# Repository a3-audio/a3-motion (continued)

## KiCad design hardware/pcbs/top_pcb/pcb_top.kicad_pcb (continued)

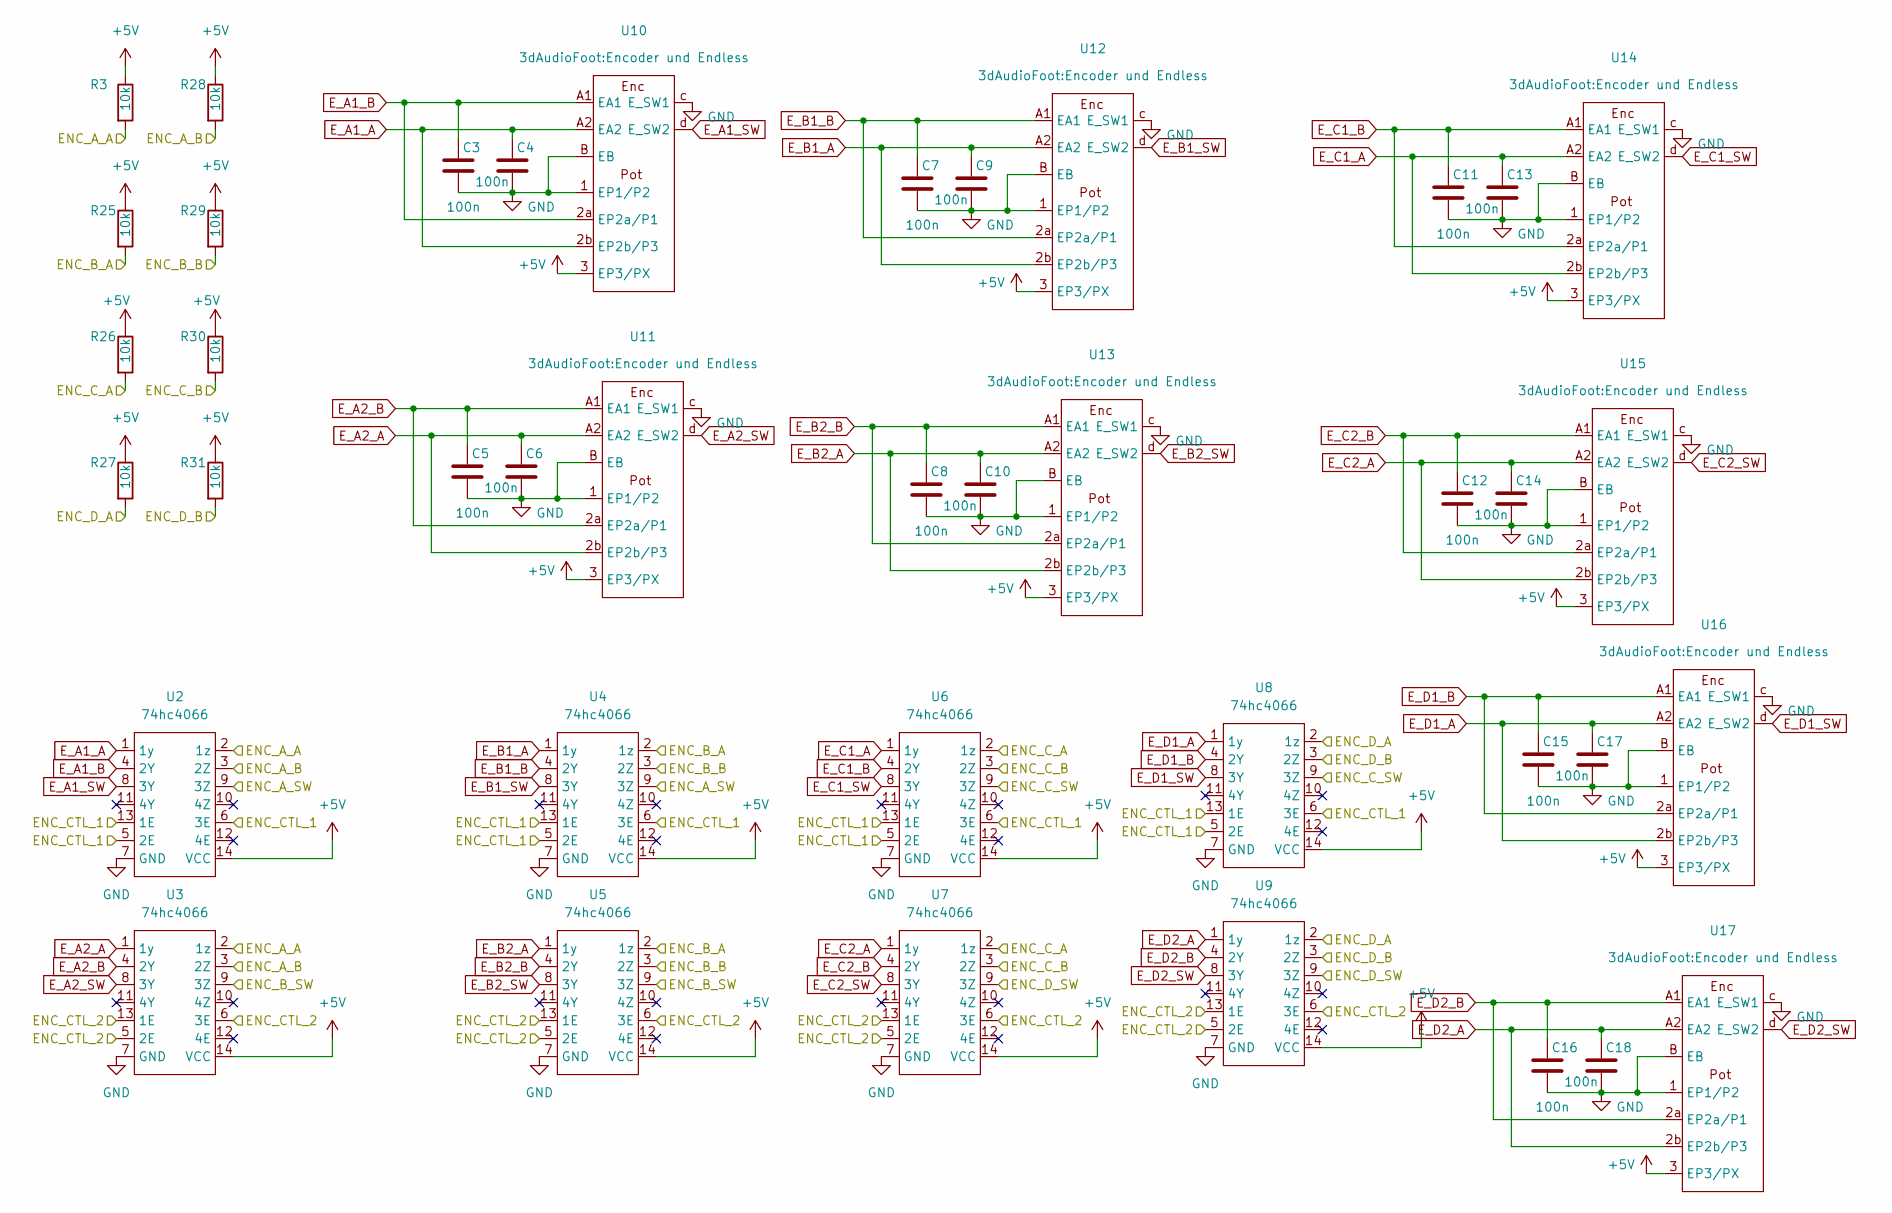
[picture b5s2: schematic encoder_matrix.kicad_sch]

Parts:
C3, C4, C5, C6, C7, C8, C9, C10, C11, C12, C13, C14, C15, C16, C17, C18: 100n; C_1206_3216Metric_Pad1.33x1.80mm_HandSolder
R3, R25, R26, R27, R28, R29, R30, R31: 10k; R_1206_3216Metric_Pad1.30x1.75mm_HandSolder
U2, U3, U4, U5, U6, U7, U8, U9: 74hc4066; SOIC-14_3.9x8.7mm_P1.27mm
U10, U11, U12, U13, U14, U15, U16, U17: Encoder und Endless

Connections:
/Untitled Sheet/ENC_A_A: R3.2, U2.2 (1z), U3.2 (1z); also elsewhere on the board
/Untitled Sheet/ENC_A_B: R28.2, U2.3 (2Z), U3.3 (2Z); also elsewhere on the board
/Untitled Sheet/ENC_A_SW: U2.9 (3Z), U4.9 (3Z); also elsewhere on the board
/Untitled Sheet/ENC_B_A: R25.2, U4.2 (1z), U5.2 (1z); also elsewhere on the board
/Untitled Sheet/ENC_B_B: R29.2, U4.3 (2Z), U5.3 (2Z); also elsewhere on the board
/Untitled Sheet/ENC_B_SW: U3.9 (3Z), U5.9 (3Z); also elsewhere on the board
/Untitled Sheet/ENC_CTL_1: U2.5 (2E), U2.6 (3E), U2.13 (1E), U4.5 (2E), U4.6 (3E), U4.13 (1E), U6.5 (2E), U6.6 (3E), U6.13 (1E), U8.5 (2E), U8.6 (3E), U8.13 (1E); also elsewhere on the board
/Untitled Sheet/ENC_CTL_2: U3.5 (2E), U3.6 (3E), U3.13 (1E), U5.5 (2E), U5.6 (3E), U5.13 (1E), U7.5 (2E), U7.6 (3E), U7.13 (1E), U9.5 (2E), U9.6 (3E), U9.13 (1E); also elsewhere on the board
/Untitled Sheet/ENC_C_A: R26.2, U6.2 (1z), U7.2 (1z); also elsewhere on the board
/Untitled Sheet/ENC_C_B: R30.2, U6.3 (2Z), U7.3 (2Z); also elsewhere on the board
/Untitled Sheet/ENC_C_SW: U6.9 (3Z), U8.9 (3Z); also elsewhere on the board
/Untitled Sheet/ENC_D_A: R27.2, U8.2 (1z), U9.2 (1z); also elsewhere on the board
/Untitled Sheet/ENC_D_B: R31.2, U8.3 (2Z), U9.3 (2Z); also elsewhere on the board
/Untitled Sheet/ENC_D_SW: U7.9 (3Z), U9.9 (3Z); also elsewhere on the board
E_A1_A: C4.1, U2.1 (1y), U10.2b (EP2b/P3), U10.A2 (EA2)
E_A1_B: C3.1, U2.4 (2Y), U10.2a (EP2a/P1), U10.A1 (EA1)
E_A1_SW: U2.8 (3Y), U10.d (E_SW2)
E_A2_A: C6.1, U3.1 (1y), U11.2b (EP2b/P3), U11.A2 (EA2)
E_A2_B: C5.1, U3.4 (2Y), U11.2a (EP2a/P1), U11.A1 (EA1)
E_A2_SW: U3.8 (3Y), U11.d (E_SW2)
E_B1_A: C9.1, U4.1 (1y), U12.2b (EP2b/P3), U12.A2 (EA2)
E_B1_B: C7.1, U4.4 (2Y), U12.2a (EP2a/P1), U12.A1 (EA1)
E_B1_SW: U4.8 (3Y), U12.d (E_SW2)
E_B2_A: C10.1, U5.1 (1y), U13.2b (EP2b/P3), U13.A2 (EA2)
E_B2_B: C8.1, U5.4 (2Y), U13.2a (EP2a/P1), U13.A1 (EA1)
E_B2_SW: U5.8 (3Y), U13.d (E_SW2)
E_C1_A: C13.1, U6.1 (1y), U14.2b (EP2b/P3), U14.A2 (EA2)
E_C1_B: C11.1, U6.4 (2Y), U14.2a (EP2a/P1), U14.A1 (EA1)
E_C1_SW: U6.8 (3Y), U14.d (E_SW2)
E_C2_A: C14.1, U7.1 (1y), U15.2b (EP2b/P3), U15.A2 (EA2)
E_C2_B: C12.1, U7.4 (2Y), U15.2a (EP2a/P1), U15.A1 (EA1)
E_C2_SW: U7.8 (3Y), U15.d (E_SW2)
E_D1_A: C17.1, U8.1 (1y), U16.2b (EP2b/P3), U16.A2 (EA2)
E_D1_B: C15.1, U8.4 (2Y), U16.2a (EP2a/P1), U16.A1 (EA1)
E_D1_SW: U8.8 (3Y), U16.d (E_SW2)
E_D2_A: C18.1, U9.1 (1y), U17.2b (EP2b/P3), U17.A2 (EA2)
E_D2_B: C16.1, U9.4 (2Y), U17.2a (EP2a/P1), U17.A1 (EA1)
E_D2_SW: U9.8 (3Y), U17.d (E_SW2)
GND: C3.2, C4.2, C5.2, C6.2, C7.2, C8.2, C9.2, C10.2, C11.2, C12.2, C13.2, C14.2, C15.2, C16.2, C17.2, C18.2, U2.7 (GND), U3.7 (GND), U4.7 (GND), U5.7 (GND), U6.7 (GND), U7.7 (GND), U8.7 (GND), U9.7 (GND), U10.1 (EP1/P2), U10.B (EB), U10.c (E_SW1), U11.1 (EP1/P2), U11.B (EB), U11.c (E_SW1), U12.1 (EP1/P2), U12.B (EB), U12.c (E_SW1), U13.1 (EP1/P2), U13.B (EB), U13.c (E_SW1), U14.1 (EP1/P2), U14.B (EB), U14.c (E_SW1), U15.1 (EP1/P2), U15.B (EB), U15.c (E_SW1), U16.1 (EP1/P2), U16.B (EB), U16.c (E_SW1), U17.1 (EP1/P2), U17.B (EB), U17.c (E_SW1); also elsewhere on the board
VCC: R3.1, R25.1, R26.1, R27.1, R28.1, R29.1, R30.1, R31.1, U2.14 (VCC), U3.14 (VCC), U4.14 (VCC), U5.14 (VCC), U6.14 (VCC), U7.14 (VCC), U8.14 (VCC), U9.14 (VCC), U10.3 (EP3/PX), U11.3 (EP3/PX), U12.3 (EP3/PX), U13.3 (EP3/PX), U14.3 (EP3/PX), U15.3 (EP3/PX), U16.3 (EP3/PX), U17.3 (EP3/PX); also elsewhere on the board

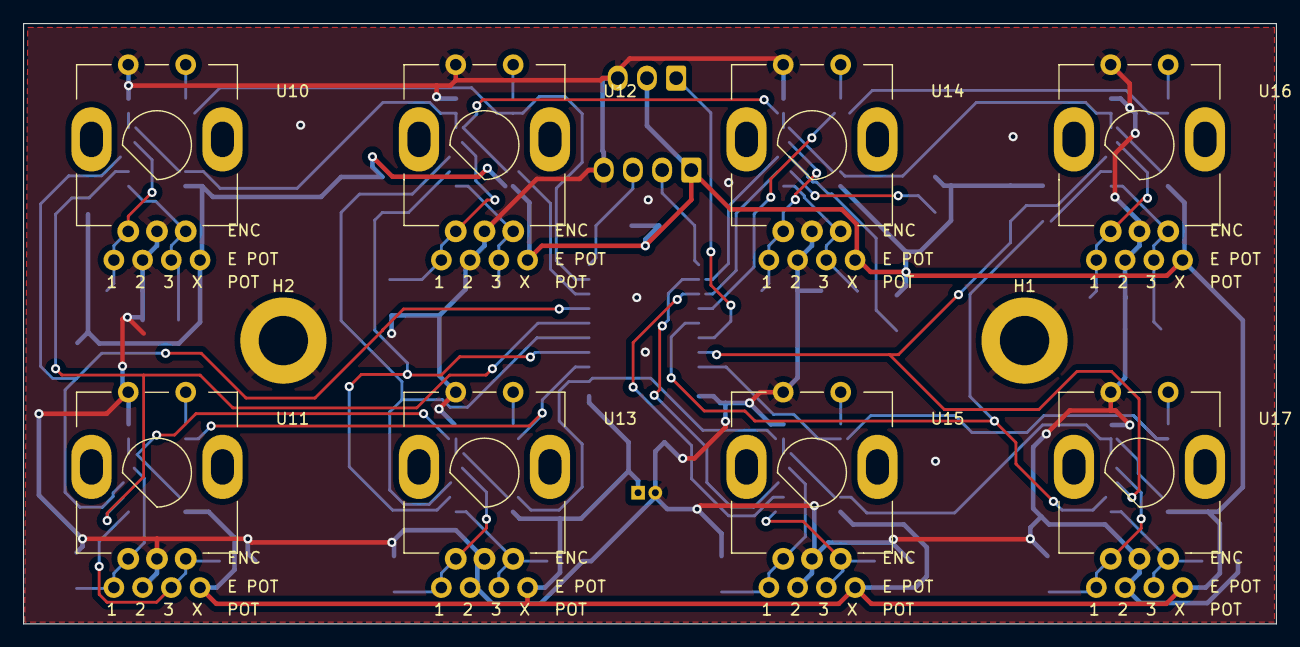
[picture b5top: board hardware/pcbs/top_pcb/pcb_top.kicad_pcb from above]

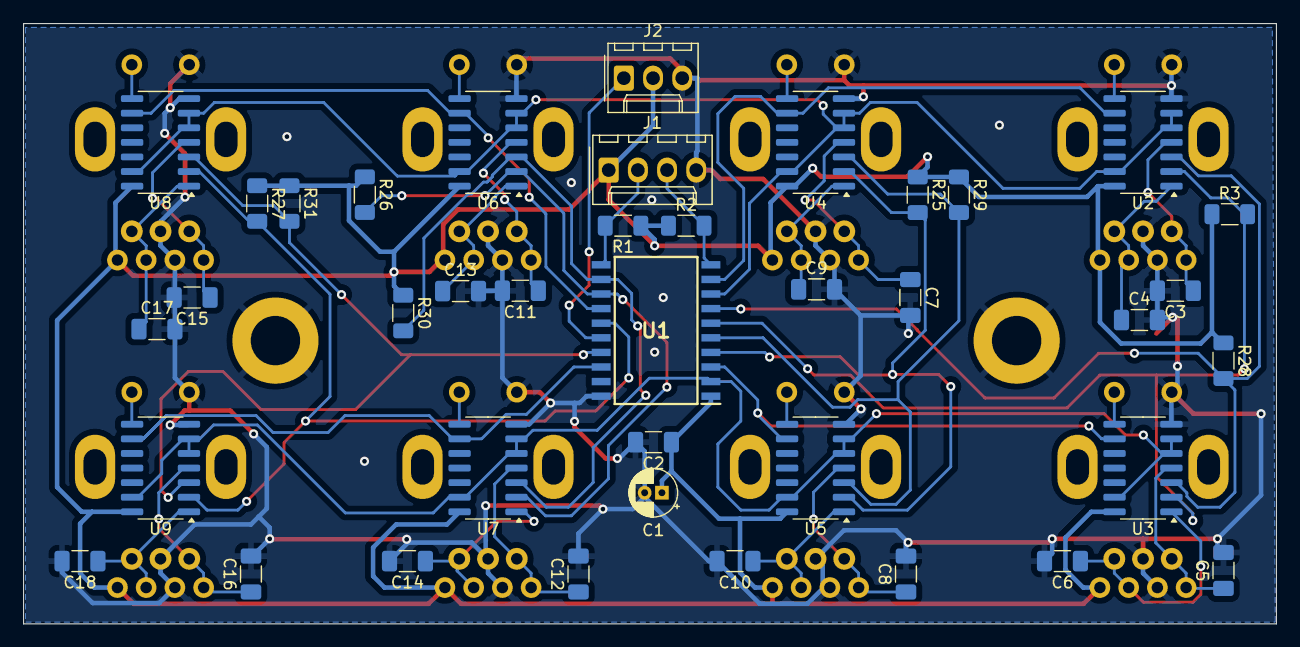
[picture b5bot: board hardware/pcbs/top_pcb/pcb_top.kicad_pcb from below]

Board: 2 copper layers, 109.0 x 52.2 mm, 49 parts (39 on the bottom side), 43 nets.

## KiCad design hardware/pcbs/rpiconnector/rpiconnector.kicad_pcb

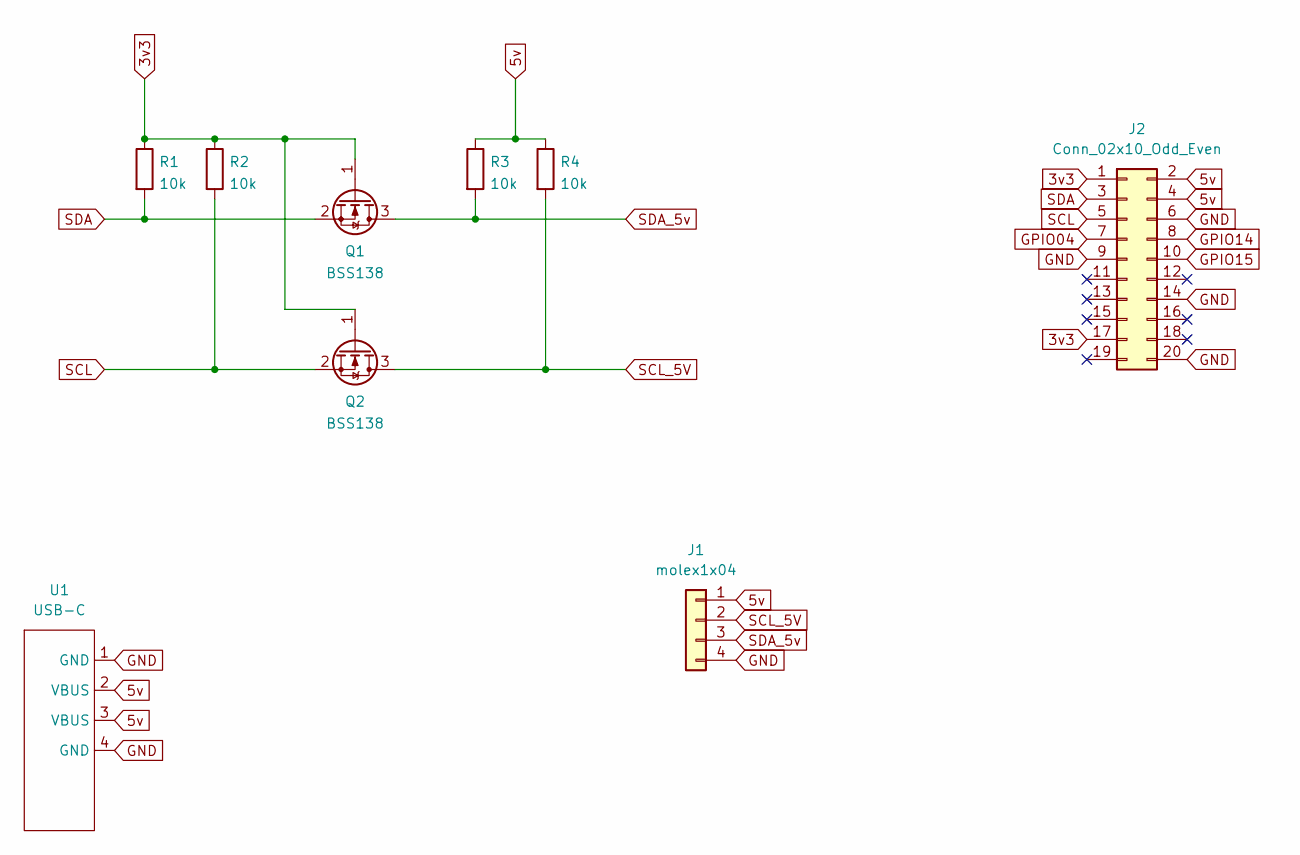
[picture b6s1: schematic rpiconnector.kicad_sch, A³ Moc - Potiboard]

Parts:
J1: molex1x04; Molex_KK-254_AE-6410-04A_1x04_P2.54mm_Vertical
J2: Conn_02x10_Odd_Even; PinSocket_2x10_P2.54mm_Vertical
Q1, Q2: BSS138
R1, R2, R3, R4: 10k; R_1206_3216Metric_Pad1.30x1.75mm_HandSolder
U1: USB-C; USB-C simple

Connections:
3v3: J2.1, J2.17, Q1.1 (G), Q2.1 (G), R1.1, R2.1
5v: J1.1, J2.2, J2.4, R3.1, R4.1, U1.2 (VBUS), U1.3 (VBUS)
GND: J1.4, J2.6, J2.9, J2.14, J2.20, U1.1 (GND), U1.4 (GND)
GPIO04: J2.7
GPIO14: J2.8
GPIO15: J2.10
SCL: J2.5, Q2.2 (S), R2.2
SCL_5V: J1.2, Q2.3 (D), R4.2
SDA: J2.3, Q1.2 (S), R1.2
SDA_5v: J1.3, Q1.3 (D), R3.2

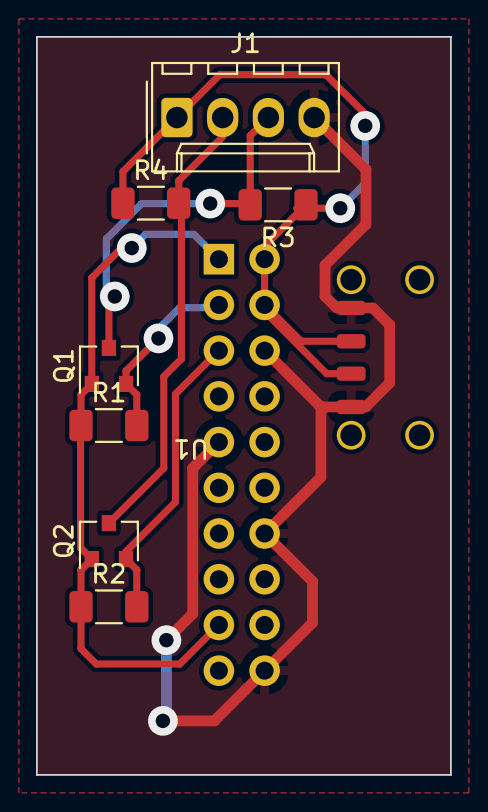
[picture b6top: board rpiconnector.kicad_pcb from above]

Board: 2 copper layers, 23.0 x 41.0 mm, 9 parts (1 on the bottom side), 7 nets.

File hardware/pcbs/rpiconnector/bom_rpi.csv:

"Reference","Value","Datasheet","Footprint","Qty","DNP"
"J1","molex1x04","~","Connector_Molex:Molex_KK-254_AE-6410-04A_1x04_P2.54mm_Vertical","1",""
"J2","Conn_02x10_Odd_Even","~","Connector_PinSocket_2.54mm:PinSocket_2x10_P2.54mm_Vertical","1",""
"Q1,Q2","BSS138","https://www.onsemi.com/pub/Collateral/BSS138-D.PDF","3dAudioFoot:BSS138","2",""
"R1,R2,R3,R4","10k","~","Resistor_SMD:R_1206_3216Metric_Pad1.30x1.75mm_HandSolder","4",""
"U1","USB-C","","3dAudioFoot:USB-C","1",""

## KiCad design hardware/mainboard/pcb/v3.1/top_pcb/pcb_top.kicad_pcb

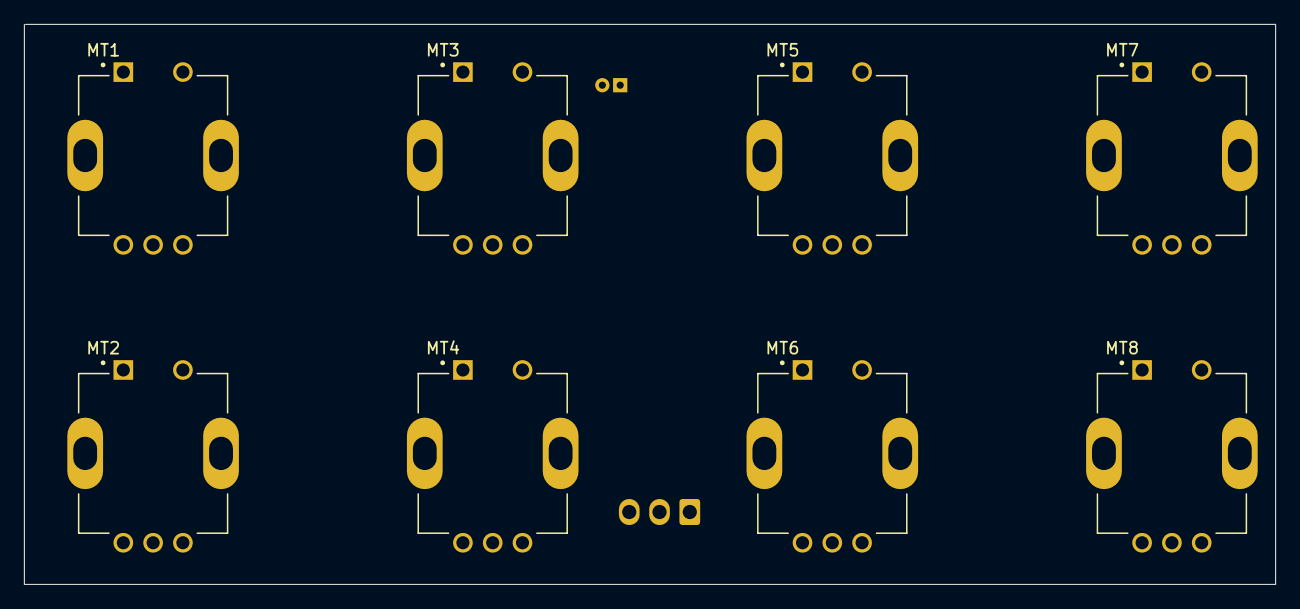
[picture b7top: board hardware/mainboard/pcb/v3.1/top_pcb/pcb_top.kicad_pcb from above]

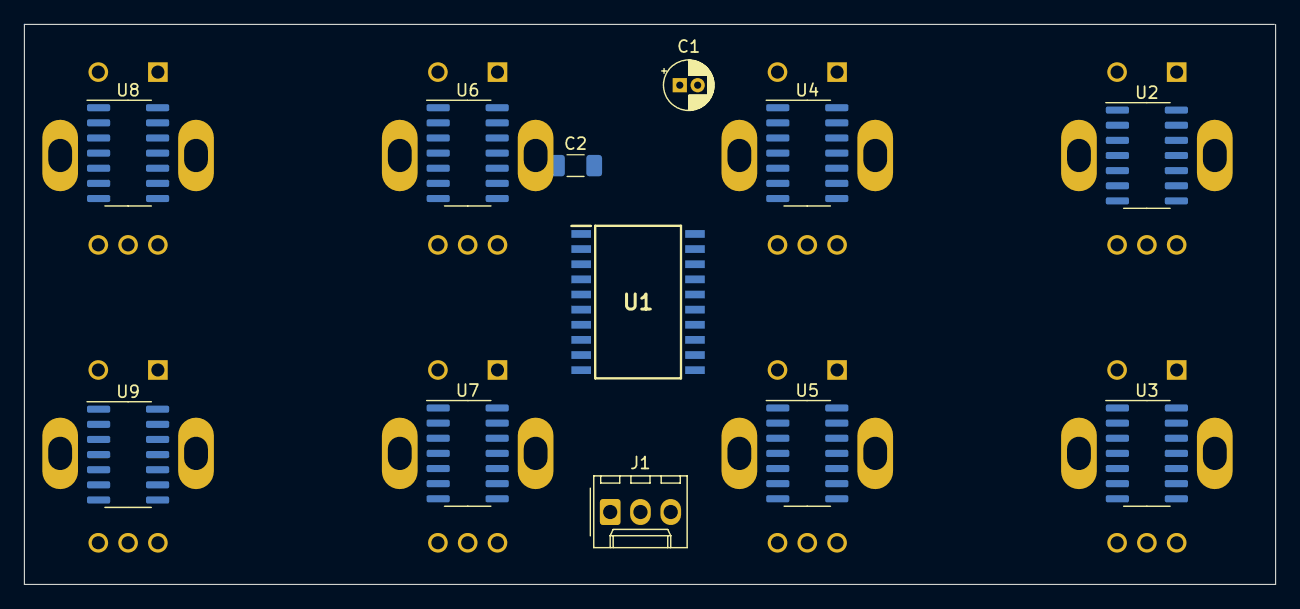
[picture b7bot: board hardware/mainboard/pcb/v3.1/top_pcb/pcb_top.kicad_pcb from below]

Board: 2 copper layers, 105.0 x 47.0 mm, 20 parts (12 on the bottom side), 43 nets, no tracks yet.

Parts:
C1: 10uF; CP_Radial_D4.0mm_P1.50mm
C2: 100nF; C_1206_3216Metric_Pad1.33x1.80mm_HandSolder
J1: molex1x03; Molex_KK-254_AE-6410-03A_1x03_P2.54mm_Vertical
MT1, MT2, MT3, MT4, MT5, MT6, MT7, MT8: PEC11R-4215F-S0024; XDCR_PEC11R-4215F-S0024
U1: ATtiny1626; attiny1626
U2, U3, U4, U5, U6, U7, U8, U9: 74hc4066; SOIC-14_3.9x8.7mm_P1.27mm

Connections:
+5V: C1.1, C2.1, U1.1 (VCC), U2.14 (VCC), U3.14 (VCC), U4.14 (VCC), U5.14 (VCC), U6.14 (VCC), U7.14 (VCC), U8.14 (VCC), U9.14 (VCC)
/Untitled Sheet/ENC_A_A: U1.4 (PA6/ADC6), U2.2 (1z), U3.2 (1z)
/Untitled Sheet/ENC_A_B: U1.5 (PA7/ADC7), U2.3 (2Z), U3.3 (2Z)
/Untitled Sheet/ENC_A_SW: U1.6 (PB5/ADC8/CLKOUT), U2.9 (3Z), U3.9 (3Z)
/Untitled Sheet/ENC_B_A: U1.7 (PB4/ADC9/RST), U4.2 (1z), U5.2 (1z)
/Untitled Sheet/ENC_B_B: U1.8 (PB3), U4.3 (2Z), U5.3 (2Z)
/Untitled Sheet/ENC_B_SW: U1.9 (PB2), U4.9 (3Z), U5.9 (3Z)
/Untitled Sheet/ENC_CTL_1: U1.2 (PA4/ADC4/SS1), U2.5 (2E), U2.6 (3E), U2.13 (1E), U4.5 (2E), U4.6 (3E), U4.13 (1E), U6.5 (2E), U6.6 (3E), U6.13 (1E), U8.5 (2E), U8.6 (3E), U8.13 (1E)
/Untitled Sheet/ENC_CTL_2: U1.3 (PA5/ADC5), U3.5 (2E), U3.6 (3E), U3.13 (1E), U5.5 (2E), U5.6 (3E), U5.13 (1E), U7.5 (2E), U7.6 (3E), U7.13 (1E), U9.5 (2E), U9.6 (3E), U9.13 (1E)
/Untitled Sheet/ENC_C_A: U1.12 (PC0/ADC12/SCK2), U6.2 (1z), U7.2 (1z)
/Untitled Sheet/ENC_C_B: U1.13 (PC1/ADC13/DO2), U6.3 (2Z), U7.3 (2Z)
/Untitled Sheet/ENC_C_SW: U1.14 (PC2/ADC14/DI2), U6.9 (3Z), U7.9 (3Z)
/Untitled Sheet/ENC_D_A: U1.15 (PC3/ADC15/SS2), U8.2 (1z), U9.2 (1z)
/Untitled Sheet/ENC_D_B: U1.17 (PA1/ADC1/DO1), U8.3 (2Z), U9.3 (2Z)
/Untitled Sheet/ENC_D_SW: U1.18 (PA2/ADC2/DI1), U8.9 (3Z), U9.9 (3Z)
E_A1_A: MT1.A, U2.1 (1y)
E_A1_B: MT1.B, U2.4 (2Y)
E_A1_SW: MT1.1, U2.8 (3Y)
E_A2_A: MT2.A, U3.1 (1y)
E_A2_B: MT2.B, U3.4 (2Y)
E_A2_SW: MT2.1, U3.8 (3Y)
E_B1_A: MT3.A, U4.1 (1y)
E_B1_B: MT3.B, U4.4 (2Y)
E_B1_SW: MT3.1, U4.8 (3Y)
E_B2_A: MT4.A, U5.1 (1y)
E_B2_B: MT4.B, U5.4 (2Y)
E_B2_SW: MT4.1, U5.8 (3Y)
E_C1_A: MT5.A, U6.1 (1y)
E_C1_B: MT5.B, U6.4 (2Y)
E_C1_SW: MT5.1, U6.8 (3Y)
E_C2_A: MT6.A, U7.1 (1y)
E_C2_B: MT6.B, U7.4 (2Y)
E_C2_SW: MT6.1, U7.8 (3Y)
E_D1_A: MT7.A, U8.1 (1y)
E_D1_B: MT7.B, U8.4 (2Y)
E_D1_SW: MT7.1, U8.8 (3Y)
E_D2_A: MT8.A, U9.1 (1y)
E_D2_B: MT8.B, U9.4 (2Y)
E_D2_SW: MT8.1, U9.8 (3Y)
GND: C1.2, C2.2, MT1.2, MT1.COM, MT1.S1 (SHIELD), MT1.S2 (SHIELD), MT2.2, MT2.COM, MT2.S1 (SHIELD), MT2.S2 (SHIELD), MT3.2, MT3.COM, MT3.S1 (SHIELD), MT3.S2 (SHIELD), MT4.2, MT4.COM, MT4.S1 (SHIELD), MT4.S2 (SHIELD), MT5.2, MT5.COM, MT5.S1 (SHIELD), MT5.S2 (SHIELD), MT6.2, MT6.COM, MT6.S1 (SHIELD), MT6.S2 (SHIELD), MT7.2, MT7.COM, MT7.S1 (SHIELD), MT7.S2 (SHIELD), MT8.2, MT8.COM, MT8.S1 (SHIELD), MT8.S2 (SHIELD), U1.20 (GND), U2.7 (GND), U3.7 (GND), U4.7 (GND), U5.7 (GND), U6.7 (GND), U7.7 (GND), U8.7 (GND), U9.7 (GND)
SCL: J1.2, U1.11 (PB0/ADC11/SCL)
SDA: J1.1, U1.10 (PB1/ADC10/SDA)
UPDI: J1.3, U1.16 (PA0/UPDI/RESET)

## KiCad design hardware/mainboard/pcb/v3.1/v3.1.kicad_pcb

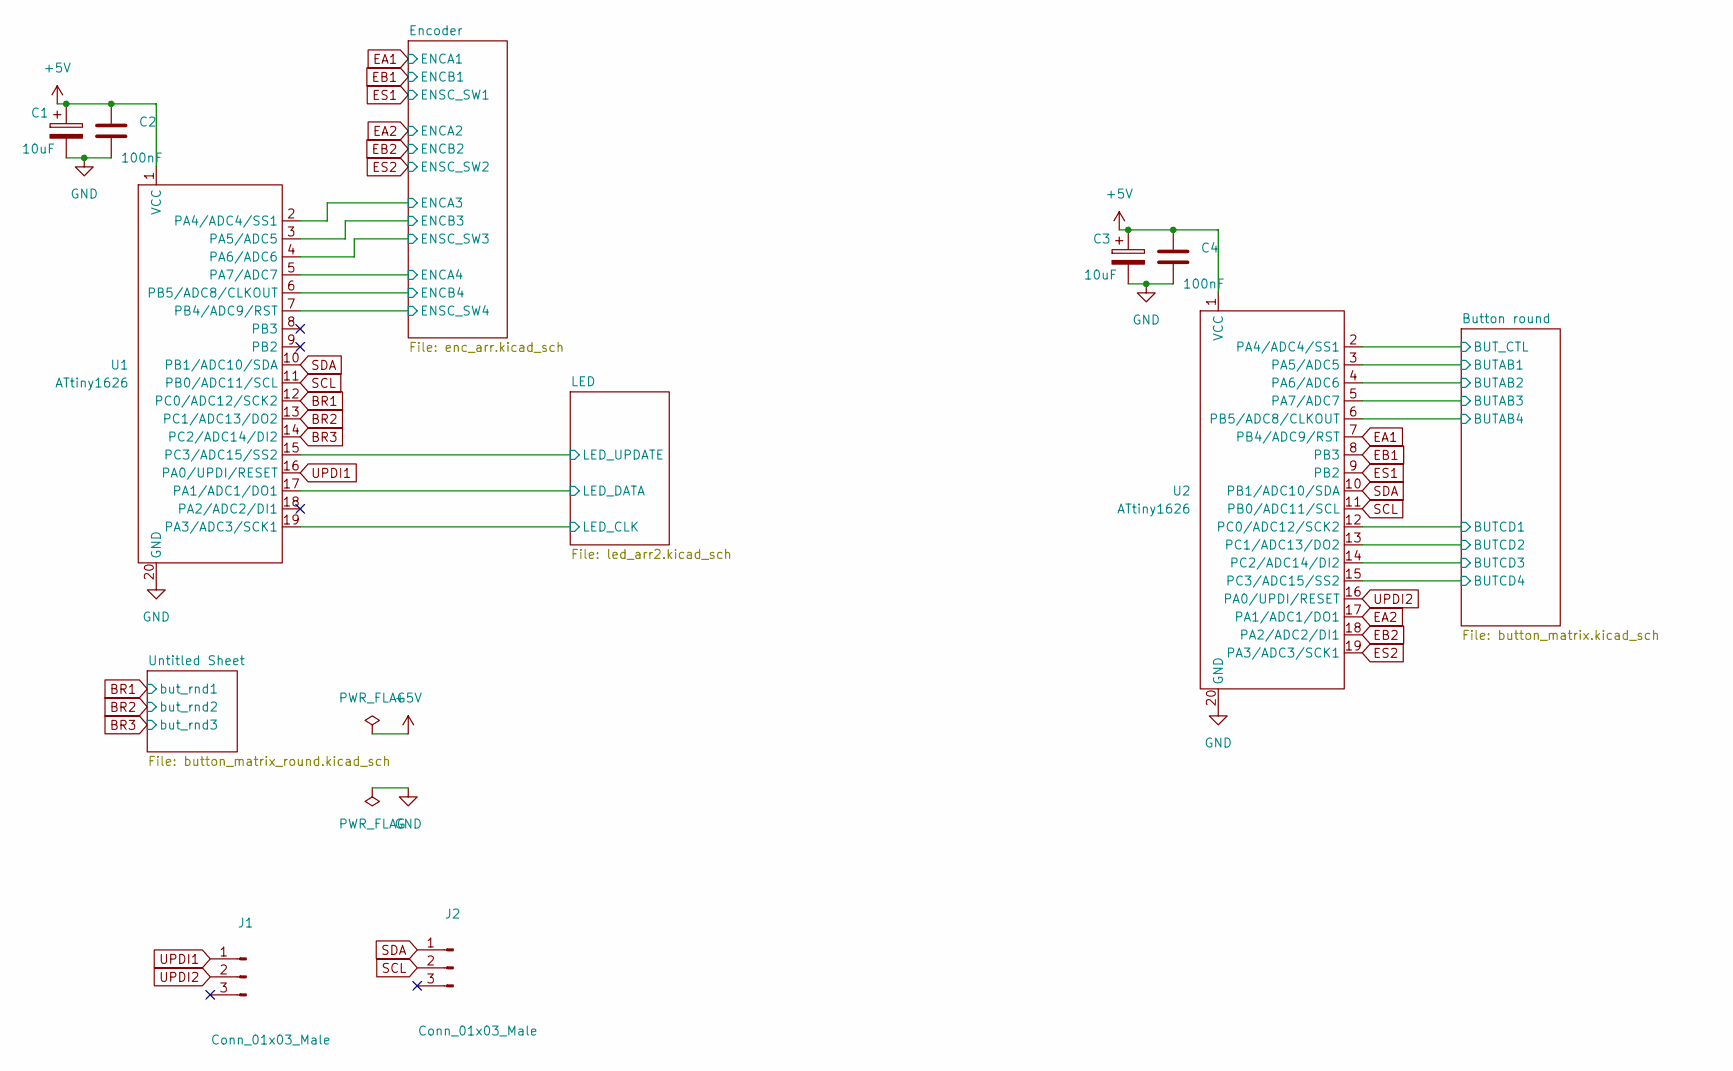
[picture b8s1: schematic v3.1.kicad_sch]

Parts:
C1, C3: 10uF; CP_Radial_D4.0mm_P1.50mm
C2, C4: 100nF; C_1206_3216Metric_Pad1.33x1.80mm_HandSolder
J1, J2: Conn_01x03_Male; Molex_KK-254_AE-6410-03A_1x03_P2.54mm_Vertical
U1, U2: ATtiny1626; attiny1626

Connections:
+5V: C1.1, C2.1, C3.1, C4.1, U1.1 (VCC), U2.1 (VCC); also elsewhere on the board
/Button round/BUTAB1: U2.3 (PA5/ADC5); also elsewhere on the board
/Button round/BUTAB2: U2.4 (PA6/ADC6); also elsewhere on the board
/Button round/BUTAB3: U2.5 (PA7/ADC7); also elsewhere on the board
/Button round/BUTAB4: U2.6 (PB5/ADC8/CLKOUT); also elsewhere on the board
/Button round/BUTCD1: U2.12 (PC0/ADC12/SCK2); also elsewhere on the board
/Button round/BUTCD2: U2.13 (PC1/ADC13/DO2); also elsewhere on the board
/Button round/BUTCD3: U2.14 (PC2/ADC14/DI2); also elsewhere on the board
/Button round/BUTCD4: U2.15 (PC3/ADC15/SS2); also elsewhere on the board
/Button round/BUT_CTL: U2.2 (PA4/ADC4/SS1); also elsewhere on the board
/Encoder/ENCA3: U1.2 (PA4/ADC4/SS1); also elsewhere on the board
/Encoder/ENCA4: U1.5 (PA7/ADC7); also elsewhere on the board
/Encoder/ENCB3: U1.3 (PA5/ADC5); also elsewhere on the board
/Encoder/ENCB4: U1.6 (PB5/ADC8/CLKOUT); also elsewhere on the board
/Encoder/ENSC_SW3: U1.4 (PA6/ADC6); also elsewhere on the board
/Encoder/ENSC_SW4: U1.7 (PB4/ADC9/RST); also elsewhere on the board
/LED/LED_CLK: U1.19 (PA3/ADC3/SCK1); also elsewhere on the board
/LED/LED_DATA: U1.17 (PA1/ADC1/DO1); also elsewhere on the board
/LED/LED_UPDATE: U1.15 (PC3/ADC15/SS2); also elsewhere on the board
BR1: U1.12 (PC0/ADC12/SCK2); also elsewhere on the board
BR2: U1.13 (PC1/ADC13/DO2); also elsewhere on the board
BR3: U1.14 (PC2/ADC14/DI2); also elsewhere on the board
EA1: U2.7 (PB4/ADC9/RST); also elsewhere on the board
EA2: U2.17 (PA1/ADC1/DO1); also elsewhere on the board
EB1: U2.8 (PB3); also elsewhere on the board
EB2: U2.18 (PA2/ADC2/DI1); also elsewhere on the board
ES1: U2.9 (PB2); also elsewhere on the board
ES2: U2.19 (PA3/ADC3/SCK1); also elsewhere on the board
GND: C1.2, C2.2, C3.2, C4.2, U1.20 (GND), U2.20 (GND); also elsewhere on the board
SCL: J2.2, U1.11 (PB0/ADC11/SCL), U2.11 (PB0/ADC11/SCL)
SDA: J2.1, U1.10 (PB1/ADC10/SDA), U2.10 (PB1/ADC10/SDA)
UPDI1: J1.1, U1.16 (PA0/UPDI/RESET)
UPDI2: J1.2, U2.16 (PA0/UPDI/RESET)

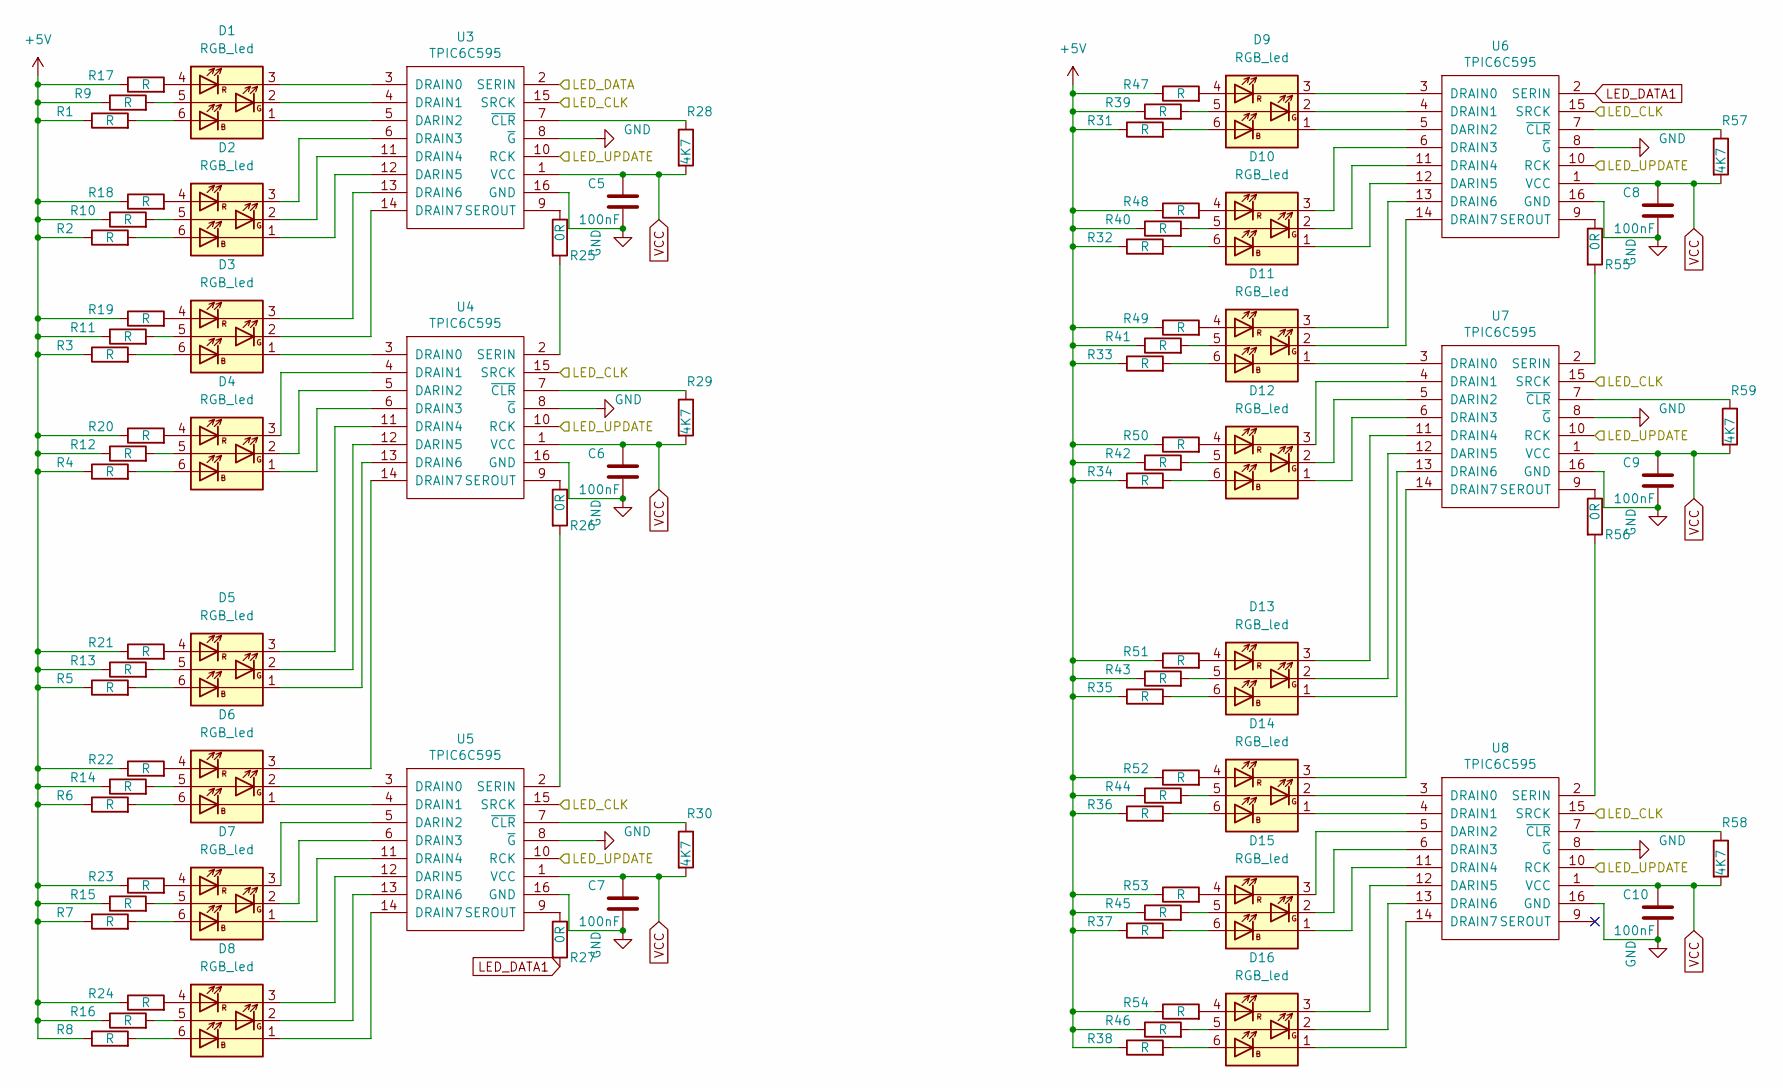
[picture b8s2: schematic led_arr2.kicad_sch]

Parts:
C5, C6, C7, C8, C9, C10: 100nF; C_1206_3216Metric_Pad1.33x1.80mm_HandSolder
D1, D2, D3, D4, D5, D6, D7, D8, D9, D10, D11, D12, D13, D14, D15, D16: RGB_led; LED_Avago_PLCC6_3x2.8mm
R1, R2, R3, R4, R5, R6, R7, R8, R9, R10, R11, R12, R13, R14, R15, R16, R17, R18, R19, R20, R21, R22, R23, R24, R31, R32, R33, R34, R35, R36, R37, R38, R39, R40, R41, R42, R43, R44, R45, R46, R47, R48, R49, R50, R51, R52, R53, R54: R; R_1206_3216Metric_Pad1.30x1.75mm_HandSolder
R25, R26, R27, R55, R56: 0R; R_1206_3216Metric_Pad1.30x1.75mm_HandSolder
R28, R29, R30, R57, R58, R59: 4K7; R_1206_3216Metric_Pad1.30x1.75mm_HandSolder
U3, U4, U5, U6, U7, U8: TPIC6C595; SOIC-16_3.9x9.9mm_P1.27mm

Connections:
+5V: R1.1, R2.1, R3.1, R4.1, R5.1, R6.1, R7.1, R8.1, R9.1, R10.1, R11.1, R12.1, R13.1, R14.1, R15.1, R16.1, R17.1, R18.1, R19.1, R20.1, R21.1, R22.1, R23.1, R24.1, R31.1, R32.1, R33.1, R34.1, R35.1, R36.1, R37.1, R38.1, R39.1, R40.1, R41.1, R42.1, R43.1, R44.1, R45.1, R46.1, R47.1, R48.1, R49.1, R50.1, R51.1, R52.1, R53.1, R54.1; also elsewhere on the board
/LED/LED_CLK: U3.15 (SRCK), U4.15 (SRCK), U5.15 (SRCK), U6.15 (SRCK), U7.15 (SRCK), U8.15 (SRCK); also elsewhere on the board
/LED/LED_DATA: U3.2 (SERIN); also elsewhere on the board
/LED/LED_UPDATE: U3.10 (RCK), U4.10 (RCK), U5.10 (RCK), U6.10 (RCK), U7.10 (RCK), U8.10 (RCK); also elsewhere on the board
GND: C5.2, C6.2, C7.2, C8.2, C9.2, C10.2, U3.8 (~G), U3.16 (GND), U4.8 (~G), U4.16 (GND), U5.8 (~G), U5.16 (GND), U6.8 (~G), U6.16 (GND), U7.8 (~G), U7.16 (GND), U8.8 (~G), U8.16 (GND); also elsewhere on the board
LED_DATA1: R27.2, U6.2 (SERIN)
unnamed: D1.1 (KB), U3.5 (DARIN2)
unnamed: D1.2 (KG), U3.4 (DRAIN1)
unnamed: D1.3 (KR), U3.3 (DRAIN0)
unnamed: D1.4 (AR), R17.2
unnamed: D1.5 (AG), R9.2
unnamed: D1.6 (AB), R1.2
unnamed: D2.1 (KB), U3.12 (DARIN5)
unnamed: D2.2 (KG), U3.11 (DRAIN4)
unnamed: D2.3 (KR), U3.6 (DRAIN3)
unnamed: D2.4 (AR), R18.2
unnamed: D2.5 (AG), R10.2
unnamed: D2.6 (AB), R2.2
unnamed: D3.1 (KB), U4.3 (DRAIN0)
unnamed: D3.2 (KG), U3.14 (DRAIN7)
unnamed: D3.3 (KR), U3.13 (DRAIN6)
unnamed: D3.4 (AR), R19.2
unnamed: D3.5 (AG), R11.2
unnamed: D3.6 (AB), R3.2
unnamed: D4.1 (KB), U4.6 (DRAIN3)
unnamed: D4.2 (KG), U4.5 (DARIN2)
unnamed: D4.3 (KR), U4.4 (DRAIN1)
unnamed: D4.4 (AR), R20.2
unnamed: D4.5 (AG), R12.2
unnamed: D4.6 (AB), R4.2
unnamed: D5.1 (KB), U4.13 (DRAIN6)
unnamed: D5.2 (KG), U4.12 (DARIN5)
unnamed: D5.3 (KR), U4.11 (DRAIN4)
unnamed: D5.4 (AR), R21.2
unnamed: D5.5 (AG), R13.2
unnamed: D5.6 (AB), R5.2
unnamed: D6.1 (KB), U5.4 (DRAIN1)
unnamed: D6.2 (KG), U5.3 (DRAIN0)
unnamed: D6.3 (KR), U4.14 (DRAIN7)
unnamed: D6.4 (AR), R22.2
unnamed: D6.5 (AG), R14.2
unnamed: D6.6 (AB), R6.2
unnamed: D7.1 (KB), U5.11 (DRAIN4)
unnamed: D7.2 (KG), U5.6 (DRAIN3)
unnamed: D7.3 (KR), U5.5 (DARIN2)
unnamed: D7.4 (AR), R23.2
unnamed: D7.5 (AG), R15.2
unnamed: D7.6 (AB), R7.2
unnamed: D8.1 (KB), U5.14 (DRAIN7)
unnamed: D8.2 (KG), U5.13 (DRAIN6)
unnamed: D8.3 (KR), U5.12 (DARIN5)
unnamed: D8.4 (AR), R24.2
unnamed: D8.5 (AG), R16.2
unnamed: D8.6 (AB), R8.2
unnamed: D9.1 (KB), U6.5 (DARIN2)
unnamed: D9.2 (KG), U6.4 (DRAIN1)
unnamed: D9.3 (KR), U6.3 (DRAIN0)
unnamed: D9.4 (AR), R47.2
unnamed: D9.5 (AG), R39.2
unnamed: D9.6 (AB), R31.2
unnamed: D10.1 (KB), U6.12 (DARIN5)
unnamed: D10.2 (KG), U6.11 (DRAIN4)
unnamed: D10.3 (KR), U6.6 (DRAIN3)
unnamed: D10.4 (AR), R48.2
unnamed: D10.5 (AG), R40.2
unnamed: D10.6 (AB), R32.2
unnamed: D11.1 (KB), U7.3 (DRAIN0)
unnamed: D11.2 (KG), U6.14 (DRAIN7)
unnamed: D11.3 (KR), U6.13 (DRAIN6)
unnamed: D11.4 (AR), R49.2
unnamed: D11.5 (AG), R41.2
unnamed: D11.6 (AB), R33.2
unnamed: D12.1 (KB), U7.6 (DRAIN3)
unnamed: D12.2 (KG), U7.5 (DARIN2)
unnamed: D12.3 (KR), U7.4 (DRAIN1)
unnamed: D12.4 (AR), R50.2
unnamed: D12.5 (AG), R42.2
unnamed: D12.6 (AB), R34.2
unnamed: D13.1 (KB), U7.13 (DRAIN6)
unnamed: D13.2 (KG), U7.12 (DARIN5)
unnamed: D13.3 (KR), U7.11 (DRAIN4)
unnamed: D13.4 (AR), R51.2
unnamed: D13.5 (AG), R43.2
unnamed: D13.6 (AB), R35.2
unnamed: D14.1 (KB), U8.4 (DRAIN1)
unnamed: D14.2 (KG), U8.3 (DRAIN0)
unnamed: D14.3 (KR), U7.14 (DRAIN7)
unnamed: D14.4 (AR), R52.2
unnamed: D14.5 (AG), R44.2
unnamed: D14.6 (AB), R36.2
unnamed: D15.1 (KB), U8.11 (DRAIN4)
unnamed: D15.2 (KG), U8.6 (DRAIN3)
unnamed: D15.3 (KR), U8.5 (DARIN2)
unnamed: D15.4 (AR), R53.2
unnamed: D15.5 (AG), R45.2
unnamed: D15.6 (AB), R37.2
unnamed: D16.1 (KB), U8.14 (DRAIN7)
unnamed: D16.2 (KG), U8.13 (DRAIN6)
unnamed: D16.3 (KR), U8.12 (DARIN5)
unnamed: D16.4 (AR), R54.2
unnamed: D16.5 (AG), R46.2
unnamed: D16.6 (AB), R38.2
unnamed: R25.1, U3.9 (SEROUT)
unnamed: R25.2, U4.2 (SERIN)
unnamed: R26.1, U4.9 (SEROUT)
unnamed: R26.2, U5.2 (SERIN)
unnamed: R27.1, U5.9 (SEROUT)
unnamed: R28.1, U3.7 (~CLR)
unnamed: R29.1, U4.7 (~CLR)
unnamed: R30.1, U5.7 (~CLR)
unnamed: R55.1, U6.9 (SEROUT)
unnamed: R55.2, U7.2 (SERIN)
unnamed: R56.1, U7.9 (SEROUT)
unnamed: R56.2, U8.2 (SERIN)
unnamed: R57.1, U6.7 (~CLR)
unnamed: R58.1, U8.7 (~CLR)
unnamed: R59.1, U7.7 (~CLR)
VCC: C5.1, C6.1, C7.1, C8.1, C9.1, C10.1, R28.2, R29.2, R30.2, R57.2, R58.2, R59.2, U3.1 (VCC), U4.1 (VCC), U5.1 (VCC), U6.1 (VCC), U7.1 (VCC), U8.1 (VCC)

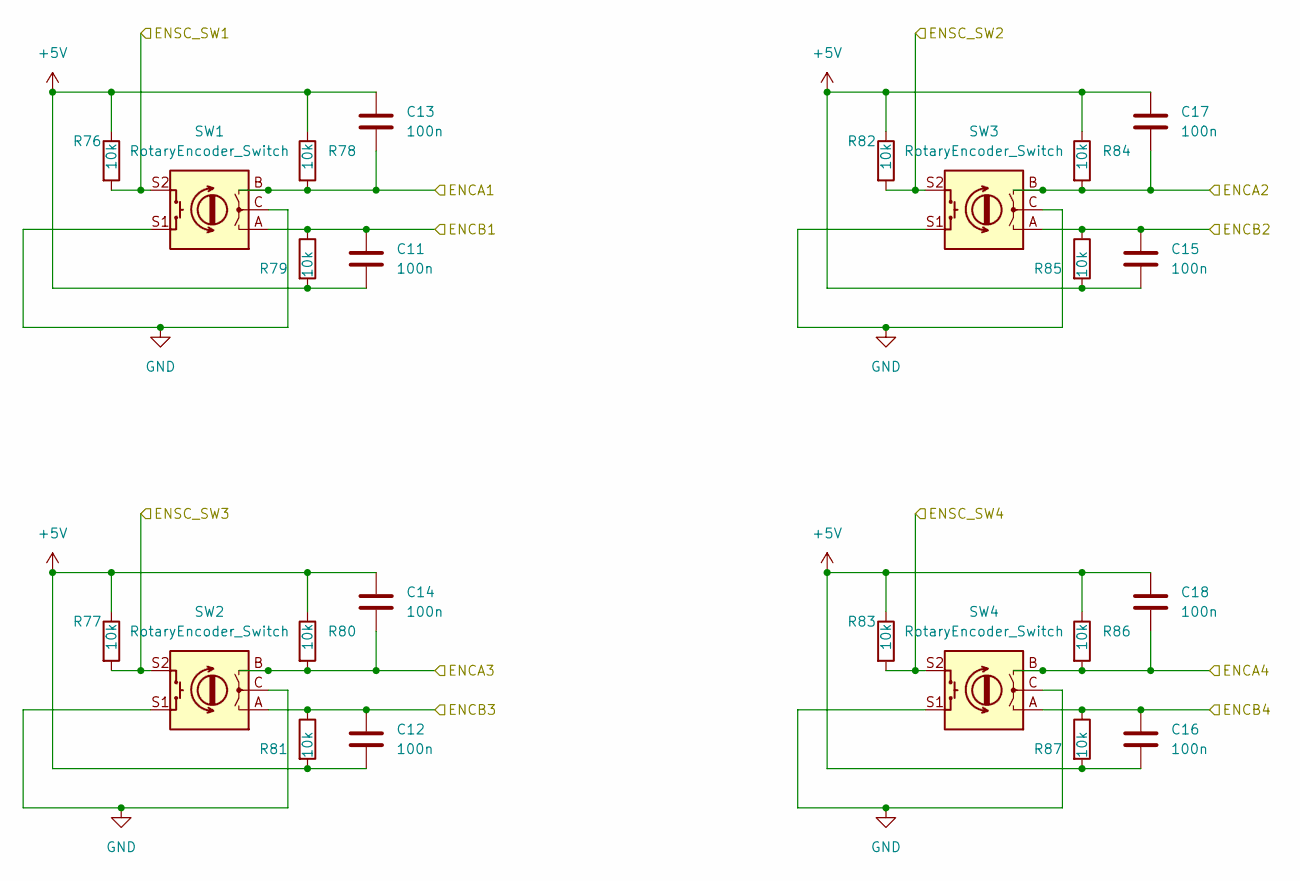
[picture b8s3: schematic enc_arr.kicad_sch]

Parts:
C11, C12, C13, C14, C15, C16, C17, C18: 100n; C_1206_3216Metric_Pad1.33x1.80mm_HandSolder
R76, R77, R78, R79, R80, R81, R82, R83, R84, R85, R86, R87: 10k; R_1206_3216Metric_Pad1.30x1.75mm_HandSolder
SW1, SW2, SW3, SW4: RotaryEncoder_Switch; PEC11R4230KS0024

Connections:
+5V: C11.2, C12.2, C13.1, C14.1, C15.2, C16.2, C17.1, C18.1, R76.1, R77.1, R78.1, R79.2, R80.1, R81.2, R82.1, R83.1, R84.1, R85.2, R86.1, R87.2; also elsewhere on the board
/Encoder/ENCA3: C14.2, R80.2, SW2.B; also elsewhere on the board
/Encoder/ENCA4: C18.2, R86.2, SW4.B; also elsewhere on the board
/Encoder/ENCB3: C12.1, R81.1, SW2.A; also elsewhere on the board
/Encoder/ENCB4: C16.1, R87.1, SW4.A; also elsewhere on the board
/Encoder/ENSC_SW3: R77.2, SW2.S2; also elsewhere on the board
/Encoder/ENSC_SW4: R83.2, SW4.S2; also elsewhere on the board
EA1: C13.2, R78.2, SW1.B; also elsewhere on the board
EA2: C17.2, R84.2, SW3.B; also elsewhere on the board
EB1: C11.1, R79.1, SW1.A; also elsewhere on the board
EB2: C15.1, R85.1, SW3.A; also elsewhere on the board
ES1: R76.2, SW1.S2; also elsewhere on the board
ES2: R82.2, SW3.S2; also elsewhere on the board
GND: SW1.C, SW1.S1, SW2.C, SW2.S1, SW3.C, SW3.S1, SW4.C, SW4.S1; also elsewhere on the board
